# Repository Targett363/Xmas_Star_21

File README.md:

# Xmas_Star_21
PCB for Xmas 2021

Branched KiCAD repo to check the feasability of diferent MCUs and shift registers

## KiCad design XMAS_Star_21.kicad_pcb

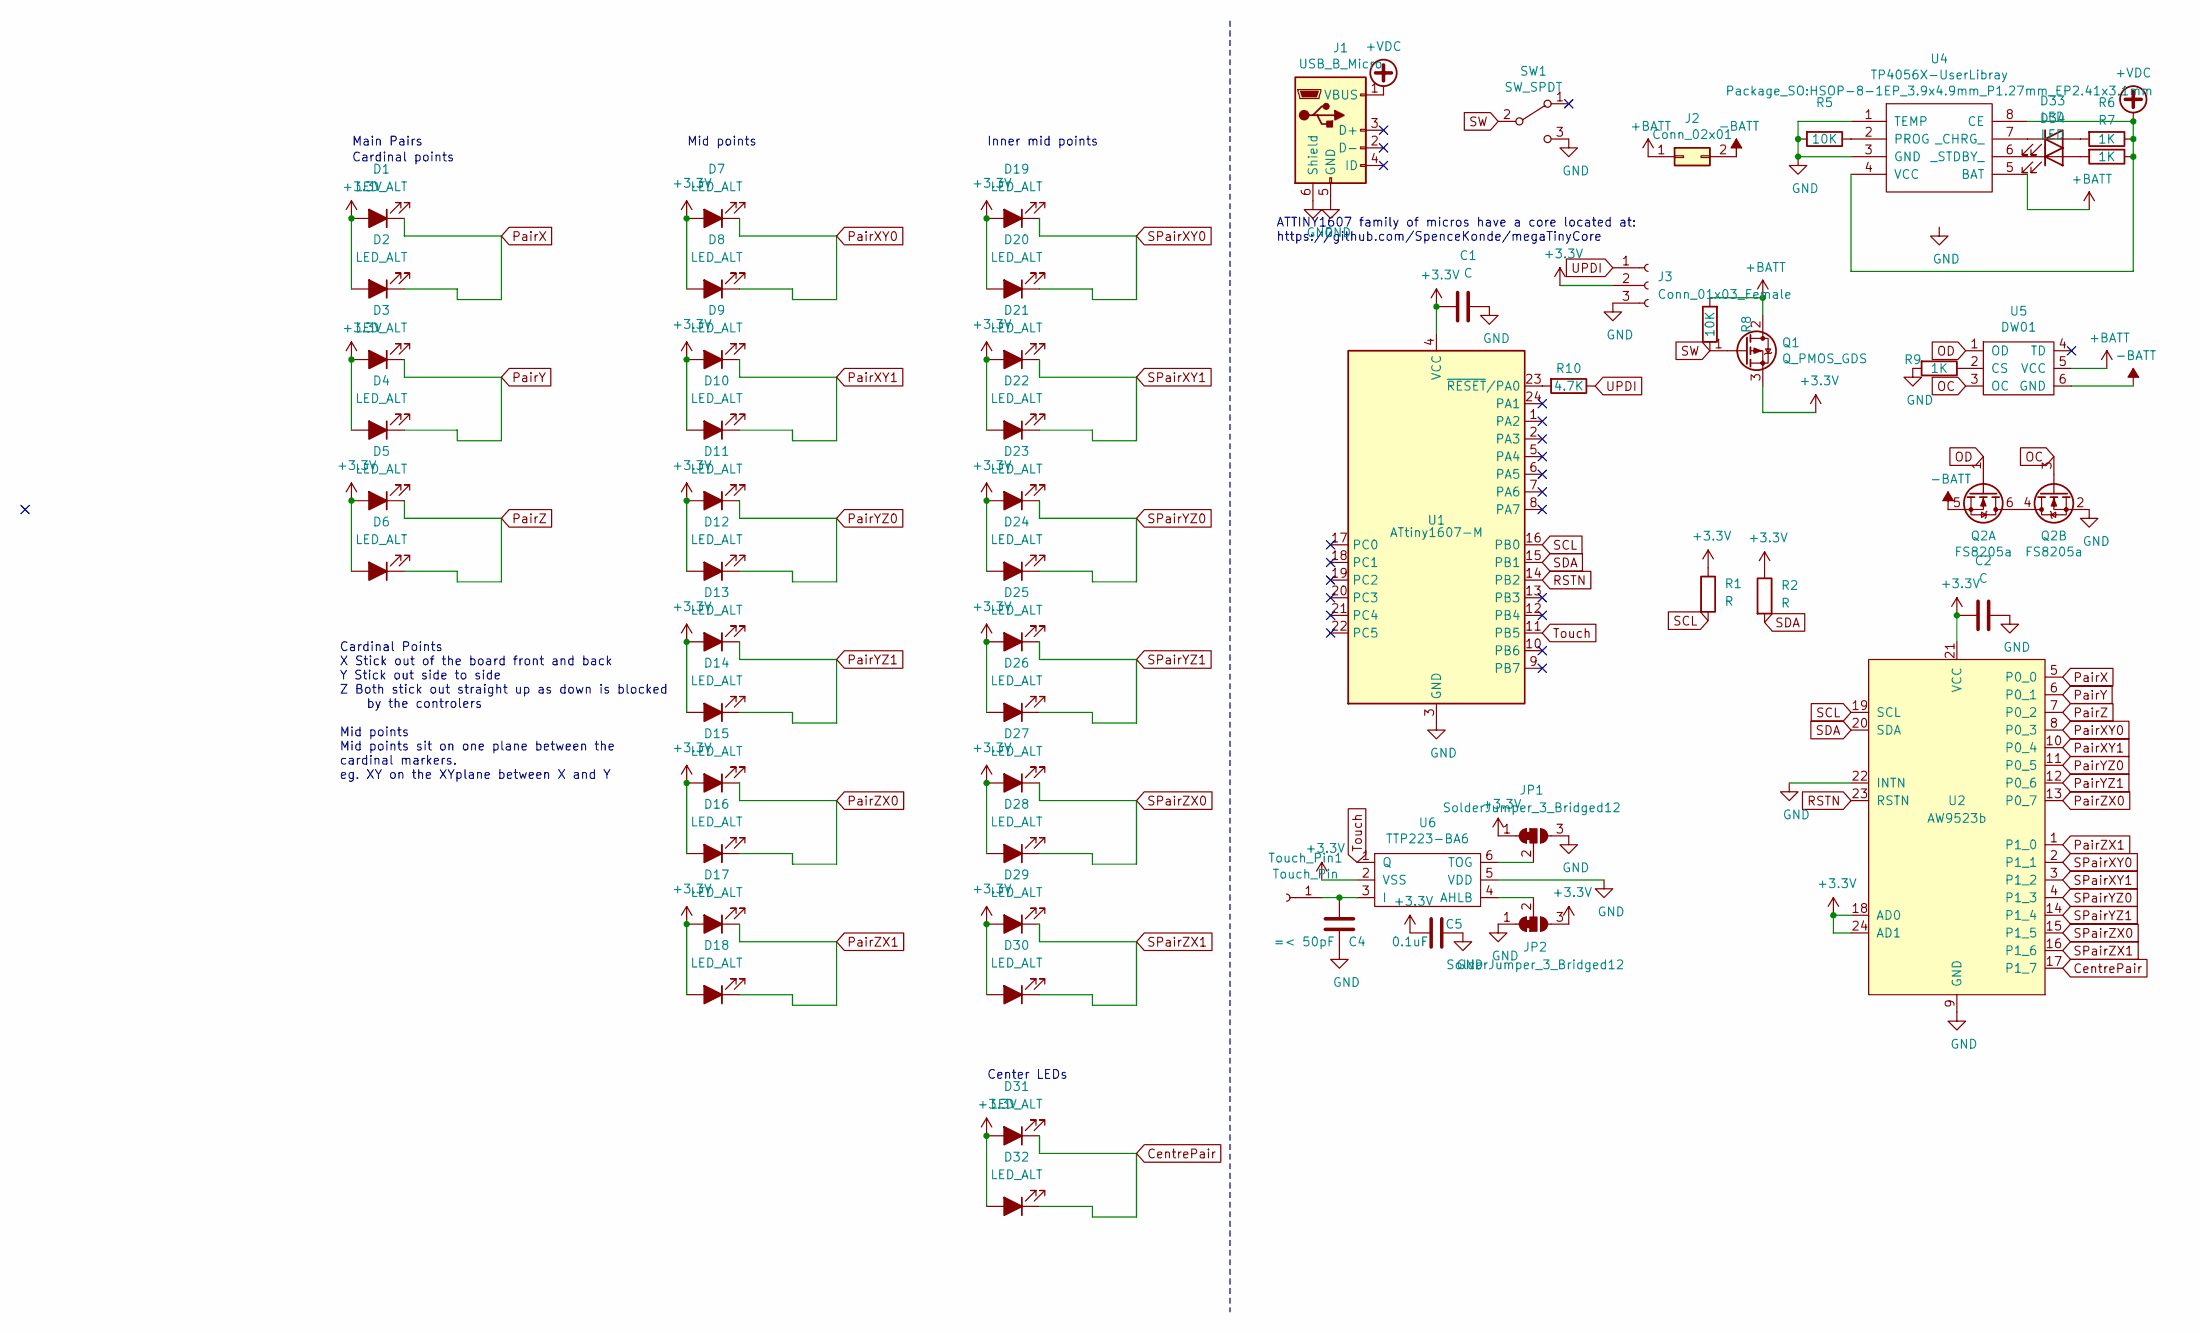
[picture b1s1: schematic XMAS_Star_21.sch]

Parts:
C1, C2: C; C_0603_1608Metric
C4: =< 50pF; C_0603_1608Metric
C5: 0.1uF; C_0603_1608Metric
D1, D2, D3, D4, D5, D6, D7, D8, D9, D10, D11, D12, D13, D14, D15, D16, D17, D18, D19, D20, D21, D22, D23, D24, D25, D26, D27, D28, D29, D30: LED_ALT; PinHeader_1x02_P1.00mm_Vertical
D31, D32: LED_ALT; LED_0603_1608Metric
D33, D34: LED; LED_0603_1608Metric_Castellated
J1: USB_B_Micro; USB_Micro-B_Molex_47346-0001
J2: Conn_02x01; JST_PH_S2B-PH-K_1x02_P2.00mm_Horizontal
J3: Conn_01x03_Female; PinSocket_1x03_P2.54mm_Vertical
JP1, JP2: SolderJumper_3_Bridged12; SolderJumper-3_P1.3mm_Bridged12_RoundedPad1.0x1.5mm_NumberL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
Q1: Q_PMOS_GDS; TO-252-2
Q2: FS8205a; SOT-23-6
R1, R2: R; R_0603_1608Metric
R5, R8: 10K; R_0603_1608Metric
R6, R7, R9: 1K; R_0603_1608Metric
R10: 4.7K; R_0603_1608Metric
SW1: SW_SPDT; SW_SPDT_PCM12
Touch_Pin1: Touch_Pin; PinHeader_1x01_P1.00mm_Vertical
U1: ATtiny1607-M; QFN-24-1EP_4x4mm_P0.5mm_EP2.6x2.6mm
U2: AW9523b; QFN-24-1EP_4x4mm_P0.5mm_EP2.7x2.7mm_ThermalVias
U4: TP4056X-UserLibray; HSOP-8-1EP_3.9x4.9mm_P1.27mm_EP2.41x3.1mm
U5: DW01; SOT-23-6
U6: TTP223-BA6; SOT-23-6

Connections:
+3V3: C1.2, C2.2, C5.2, D1.2 (A), D2.2 (A), D3.2 (A), D4.2 (A), D5.2 (A), D6.2 (A), D7.2 (A), D8.2 (A), D9.2 (A), D10.2 (A), D11.2 (A), D12.2 (A), D13.2 (A), D14.2 (A), D15.2 (A), D16.2 (A), D17.2 (A), D18.2 (A), D19.2 (A), D20.2 (A), D21.2 (A), D22.2 (A), D23.2 (A), D24.2 (A), D25.2 (A), D26.2 (A), D27.2 (A), D28.2 (A), D29.2 (A), D30.2 (A), D31.2 (A), D32.2 (A), J3.2, JP1.1 (A), JP2.3 (B), Q1.3 (S), R1.1, R2.1, U1.4 (VCC), U2.18 (AD0), U2.21 (VCC), U2.24 (AD1), U6.2 (VSS)
+BATT: J2.1, Q1.2 (D), R8.2, U4.5 (BAT), U5.5 (VCC)
+VDC: J1.1 (VBUS), R6.1, R7.1, U4.4 (VCC), U4.8 (CE)
-BATT: J2.2, Q2.5 (S), U5.6 (GND)
CentrePair: D31.1 (K), D32.1 (K), U2.17 (P1_7)
GND: C1.1, C2.1, C4.1, C5.1, J1.5 (GND), J1.6 (Shield), J3.3, JP1.3 (B), JP2.1 (A), Q2.2 (S), R5.2, R9.2, SW1.3 (C), U1.3 (GND), U1.25 (GND), U2.9 (GND), U2.22 (INTN), U2.25 (GND), U4.1 (TEMP), U4.3 (GND), U4.9 (GND), U6.5 (VDD)
unnamed: C4.2, Touch_Pin1.1, U6.3 (I)
unnamed: D33.1 (K), U4.7 (_CHRG_)
unnamed: D33.2 (A), R6.2
unnamed: D34.1 (K), U4.6 (_STDBY_)
unnamed: D34.2 (A), R7.2
unnamed: JP1.2 (C), U6.6 (TOG)
unnamed: JP2.2 (C), U6.4 (AHLB)
unnamed: Q2.4 (D), Q2.6 (D)
unnamed: R5.1, U4.2 (PROG)
unnamed: R9.1, U5.2 (CS)
unnamed: R10.2, U1.23 (~RESET~/PA0)
OC: Q2.3 (G), U5.3 (OC)
OD: Q2.1 (G), U5.1 (OD)
PairX: D1.1 (K), D2.1 (K), U2.5 (P0_0)
PairXY0: D7.1 (K), D8.1 (K), U2.8 (P0_3)
PairXY1: D9.1 (K), D10.1 (K), U2.10 (P0_4)
PairY: D3.1 (K), D4.1 (K), U2.6 (P0_1)
PairYZ0: D11.1 (K), D12.1 (K), U2.11 (P0_5)
PairYZ1: D13.1 (K), D14.1 (K), U2.12 (P0_6)
PairZ: D5.1 (K), D6.1 (K), U2.7 (P0_2)
PairZX0: D15.1 (K), D16.1 (K), U2.13 (P0_7)
PairZX1: D17.1 (K), D18.1 (K), U2.1 (P1_0)
RSTN: U1.14 (PB2), U2.23 (RSTN)
SCL: R1.2, U1.16 (PB0), U2.19 (SCL)
SDA: R2.2, U1.15 (PB1), U2.20 (SDA)
SPairXY0: D19.1 (K), D20.1 (K), U2.2 (P1_1)
SPairXY1: D21.1 (K), D22.1 (K), U2.3 (P1_2)
SPairYZ0: D23.1 (K), D24.1 (K), U2.4 (P1_3)
SPairYZ1: D25.1 (K), D26.1 (K), U2.14 (P1_4)
SPairZX0: D27.1 (K), D28.1 (K), U2.15 (P1_5)
SPairZX1: D29.1 (K), D30.1 (K), U2.16 (P1_6)
SW: Q1.1 (G), R8.1, SW1.2 (B)
Touch: U1.11 (PB5), U6.1 (Q)
UPDI: J3.1, R10.1

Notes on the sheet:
Main Pairs
Cardinal points
Mid points
Cardinal Points X Stick out of the board front and back Y Stick out side to side Z Both stick out straight up as down is blocked by the controlers Mid points Mid points sit on one plane between the cardinal markers. eg. XY on the XYplane between X and Y
Inner mid points
Center LEDs
ATTINY1607 family of micros have a core located at: https://github.com/SpenceKonde/megaTinyCore

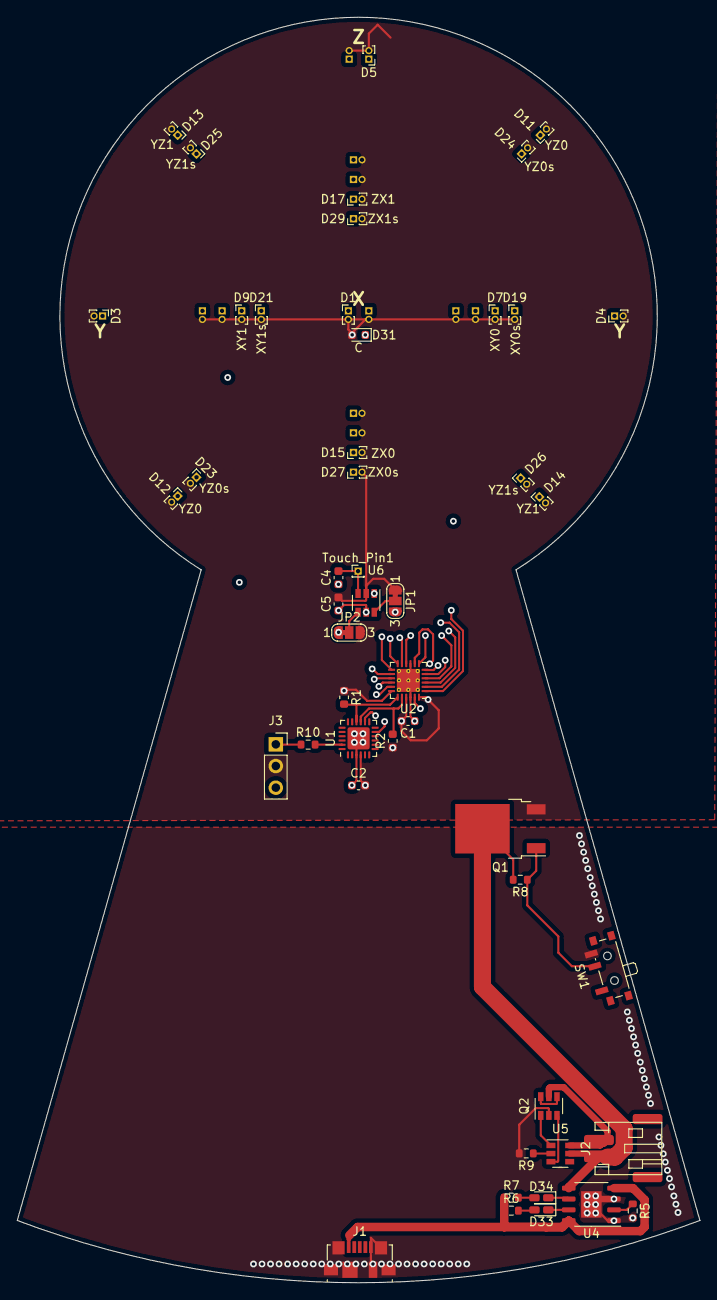
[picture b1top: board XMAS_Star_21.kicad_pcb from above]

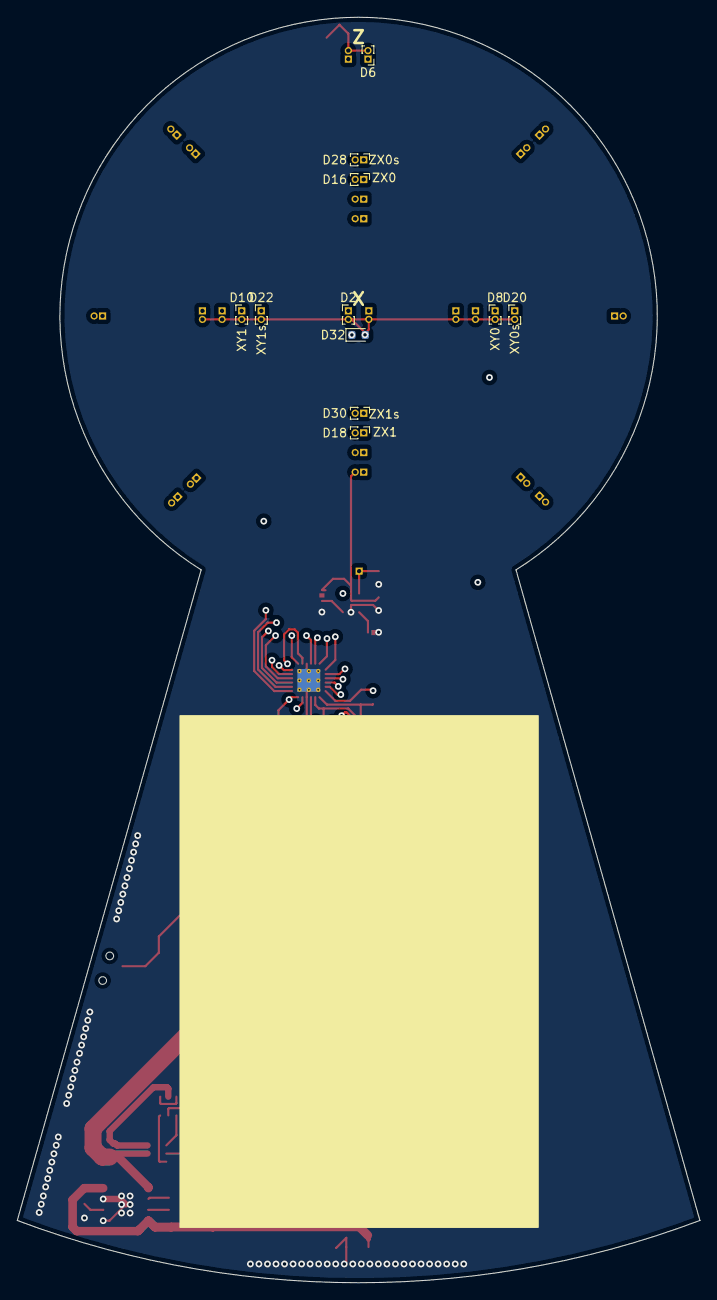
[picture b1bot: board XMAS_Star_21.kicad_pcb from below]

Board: 4 copper layers, 80.0 x 148.3 mm, 60 parts (11 on the bottom side), 40 nets.

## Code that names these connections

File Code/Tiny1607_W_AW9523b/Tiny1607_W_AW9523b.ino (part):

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 * Touch input from TTP223-BA6.
 * 
 * Pins:
 * Touch   - Arduino Pin 6,  Port name PB5, Physical 11
 * i2c SCL - Arduino Pin 11, Port name PB0, Physical 16
 * i2c SDA - Arduino Pin 10, Port name PB1, Physical 15
 * AW RSTN - Arduino Pin 9,  Port name PB2, Physical 14
 * 
 * AW9523b i2c address is set as high high so 0b1011011 plus the R/W bit on the end
 * 
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
//PIN Names
const int TouchPin = 6;
const int RSTN = 9;
const int LED = 2;

//AW9523 i2c names
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
void setup() {
  cli(); //disable interrupts
  pinMode(TouchPin,INPUT); //Set Touch pin to input mode
  PORTB.PIN5CTRL|=0x01; //Set Touch pin to interrupt on rising edge and falling edge input as TTP223 is set to toggle on touch
  sei(); //enable interrupts
  
  pinMode(RSTN, OUTPUT); //Set the AW9523b reset to HIGH to prevent reset state before startup
  digitalWrite(RSTN, HIGH);
  
  Wire.begin();
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ISR(PORTB_PORT_vect){
  cli(); //disable interrupts
  byte flags=PORTB.INTFLAGS; //Read the Port B interrupt flags
  PORTB.INTFLAGS=0x20;       //Clear the interrupt flag for Touch pin so as to leave any other interrupt that triggered on Port B flagged for i2c
  if (flags&0x20){           //if it was triggered by pin5
    interrupted = HIGH;      //set program interrupted flag to end animation and re-enter the loop
    prog++;                  //then increment the program counter by 1
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
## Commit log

2021-01-01 Initial Star files
2021-01-01 cleaning autosaves
2021-01-01 Swapping the shift register for AW9523b
2021-01-01 Added AW9523b and required nets to schematic
2021-01-01 Added AW9523b and routing to PCB
2021-01-03 Adding Readme and Extras
2021-01-05 AW9523b datasheet in English
2021-01-06 cleaned up UDPI connector
2021-01-06 tidy power to ICs and start code
2021-01-06 hashing out the shape of the Arduino flow
2021-01-06 Remembering to put pullups on the i2cgit add --all
2021-01-07 further shaping of the code and change TTP223 from direct to toggle output
2021-01-07 updated interrupt in code for the change of TTP223 from direct to toggle output
2021-01-08 adding the i2c transmit animation function and making it work
2021-01-08 Gerbers made, zipped and sent
2021-01-08 fix silly curly brace mistake
2021-01-18 Code updates, allow Animations to run forward and reverse, added Fade animation
2021-01-18 Code update, added number of repeats variable to animation function
2021-01-18 Code update, added number of repeats variable to animation function. With comments this time
2021-01-18 Added another animation
2021-03-12 Added debug flash to code
2021-03-13 continuing to play with code
